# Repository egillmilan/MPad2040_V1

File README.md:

# MPad2040_V1
Numpad based on the RP2040 microcontroller. Uses USB-C and has a macro-row at the top. [Schematic can be found here.](https://github.com/egillmilan/MPad2040_V1/files/11053267/MPad2040_V1.pdf)

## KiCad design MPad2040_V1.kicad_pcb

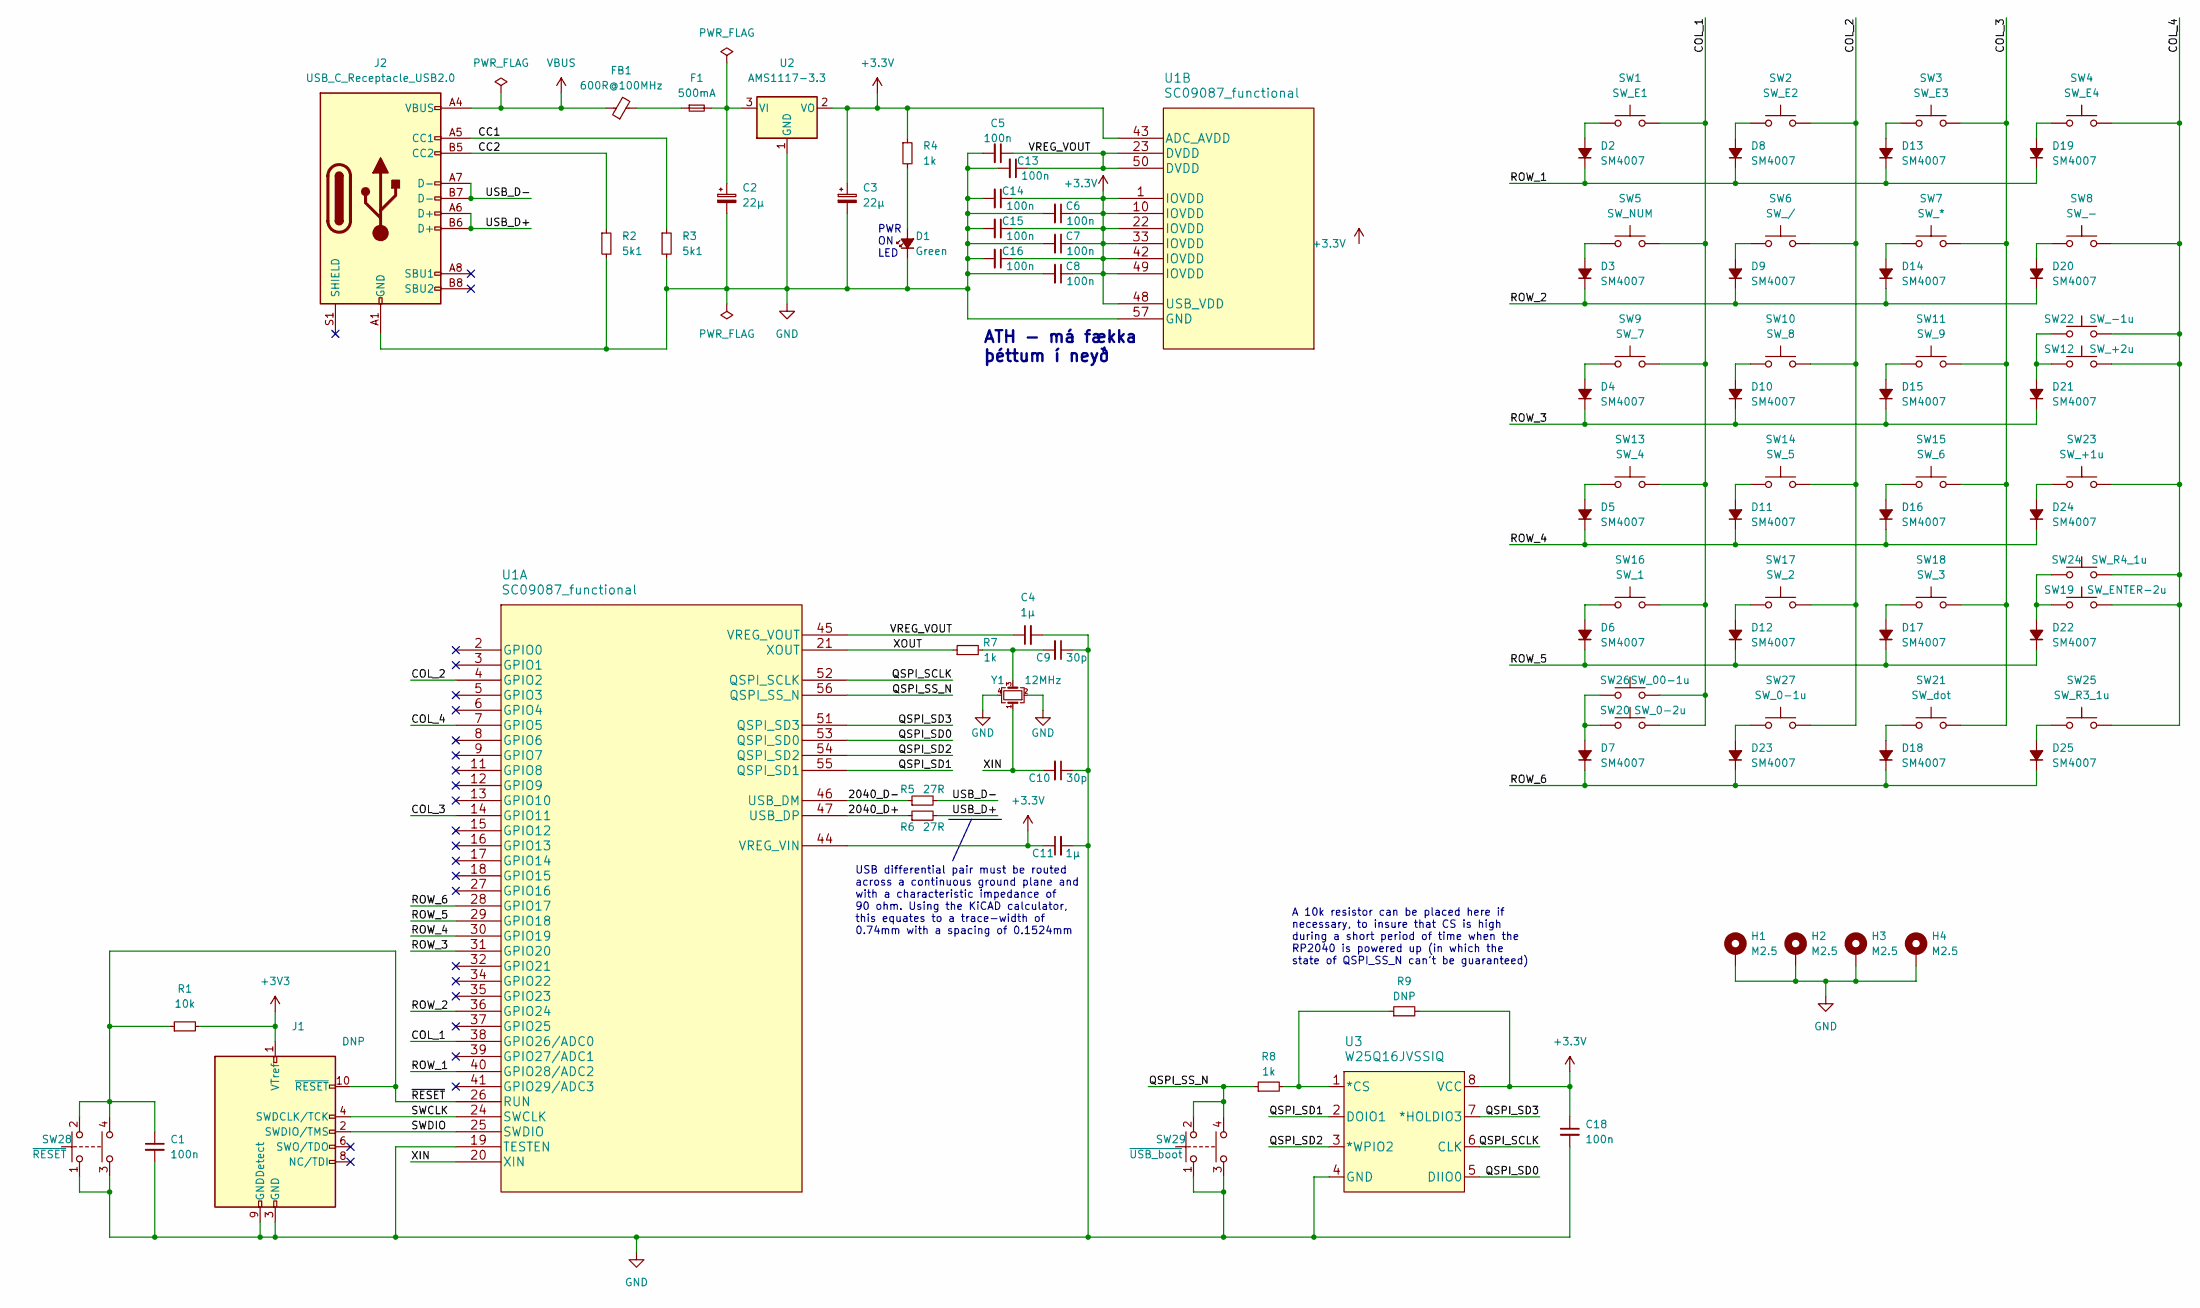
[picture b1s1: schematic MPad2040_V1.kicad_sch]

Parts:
C1, C5, C6, C7, C8, C13, C14, C15, C16, C18: 100n; C_0402_1005Metric
C2, C3: 22µ; CP_EIA-3216-18_Kemet-A
C4, C11: 1µ; C_0402_1005Metric
C9, C10: 30p; C_0402_1005Metric
D1: Green; LED_0603_1608Metric
D2, D3, D4, D5, D6, D7, D8, D9, D10, D11, D12, D13, D14, D15, D16, D17, D18, D19, D20, D21, D22, D23, D24, D25: SM4007; D_SOD-123F
F1: 500mA; Fuse_1206_3216Metric
FB1: 600R@100MHz; L_0603_1608Metric
H1, H2, H3, H4: M2.5; MountingHole_2.7mm_M2.5_Pad_Via
J1: DNP; PinSocket_2x05_P1.27mm_Vertical_SMD
J2: USB_C_Receptacle_USB2.0; USB_C_Receptacle_GCT_USB4085
R1: 10k; R_0603_1608Metric
R2, R3: 5k1; R_0603_1608Metric
R4, R7, R8: 1k; R_0603_1608Metric
R5, R6: 27R; R_0603_1608Metric
R9: DNP; R_0603_1608Metric
SW1: SW_E1; SW_Cherry_MX_1.00u_R1
SW2: SW_E2; SW_Cherry_MX_1.00u_R1
SW3: SW_E3; SW_Cherry_MX_1.00u_R1
SW4: SW_E4; SW_Cherry_MX_1.00u_R1
SW5: SW_NUM; SW_Cherry_MX_1.00u_R1
SW6: SW_/; SW_Cherry_MX_1.00u_R1
SW7: SW_*; SW_Cherry_MX_1.00u_R1
SW8: SW_-; SW_Cherry_MX_1.00u_R1
SW9: SW_7; SW_Cherry_MX_1.00u_R3
SW10: SW_8; SW_Cherry_MX_1.00u_R3
SW11: SW_9; SW_Cherry_MX_1.00u_R3
SW12: SW_+2u; SW_Cherry_MX_2.00u_Vertical_PCB
SW13: SW_4; SW_Cherry_MX_1.00u_R3
SW14: SW_5; SW_Cherry_MX_1.00u_R3
SW15: SW_6; SW_Cherry_MX_1.00u_R3
SW16: SW_1; SW_Cherry_MX_1.00u_R4
SW17: SW_2; SW_Cherry_MX_1.00u_R4
SW18: SW_3; SW_Cherry_MX_1.00u_R4
SW19: SW_ENTER-2u; SW_Cherry_MX_2.00u_Vertical_PCB
SW20: SW_0-2u; SW_Cherry_MX_2.00u_PCB
SW21: SW_dot; SW_Cherry_MX_1.00u_R3
SW22: SW_-1u; SW_Cherry_MX_1.00u_R2
SW23: SW_+1u; SW_Cherry_MX_1.00u_R3
SW24: SW_R4_1u; SW_Cherry_MX_1.00u_R4
SW25: SW_R3_1u; SW_Cherry_MX_1.00u_R3
SW26: SW_00-1u; SW_Cherry_MX_1.00u_R3
SW27: SW_0-1u; SW_Cherry_MX_1.00u_R3
SW28: ~{RESET}; SW_TS-1187A-B-A-B
SW29: ~{USB_boot}; SW_TS-1187A-B-A-B
U1: SC09087_functional; SC09087
U2: AMS1117-3.3; SOT-223-3_TabPin2
U3: W25Q16JVSSIQ
Y1: 12MHz; Crystal_SMD_3225-4Pin_3.2x2.5mm

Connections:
/2040_D+: R6.1, U1.47 (USB_DP)
/2040_D-: R5.1, U1.46 (USB_DM)
/CC1: J2.A5 (CC1), R3.1
/CC2: J2.B5 (CC2), R2.1
/COL_1: SW1.2, SW5.2, SW9.2, SW13.2, SW16.2, SW20.2, SW26.2, U1.38 (GPIO26/ADC0)
/COL_2: SW2.2, SW6.2, SW10.2, SW14.2, SW17.2, SW27.2, U1.4 (GPIO2)
/COL_3: SW3.2, SW7.2, SW11.2, SW15.2, SW18.2, SW21.2, U1.14 (GPIO11)
/COL_4: SW4.2, SW8.2, SW12.2, SW19.2, SW22.2, SW23.2, SW24.2, SW25.2, U1.7 (GPIO5)
/QSPI_SCLK: U1.52 (QSPI_SCLK), U3.6 (CLK)
/QSPI_SD0: U1.53 (QSPI_SD0), U3.5 (DIIO0)
/QSPI_SD1: U1.55 (QSPI_SD1), U3.2 (DOIO1)
/QSPI_SD2: U1.54 (QSPI_SD2), U3.3 (*WPIO2)
/QSPI_SD3: U1.51 (QSPI_SD3), U3.7 (*HOLDIO3)
/QSPI_SS_N: R8.1, SW29.2, SW29.4, U1.56 (QSPI_SS_N)
/ROW_1: D2.1 (K), D8.1 (K), D13.1 (K), D19.1 (K), U1.40 (GPIO28/ADC2)
/ROW_2: D3.1 (K), D9.1 (K), D14.1 (K), D20.1 (K), U1.36 (GPIO24)
/ROW_3: D4.1 (K), D10.1 (K), D15.1 (K), D21.1 (K), U1.31 (GPIO20)
/ROW_4: D5.1 (K), D11.1 (K), D16.1 (K), D24.1 (K), U1.30 (GPIO19)
/ROW_5: D6.1 (K), D12.1 (K), D17.1 (K), D22.1 (K), U1.29 (GPIO18)
/ROW_6: D7.1 (K), D18.1 (K), D23.1 (K), D25.1 (K), U1.28 (GPIO17)
/SWCLK: J1.4 (SWDCLK/TCK), U1.24 (SWCLK)
/SWDIO: J1.2 (SWDIO/TMS), U1.25 (SWDIO)
/USB_D+: J2.A6 (D+), J2.B6 (D+), R6.2
/USB_D-: J2.A7 (D-), J2.B7 (D-), R5.2
/VREG_VOUT: C4.1, C5.1, C13.1, U1.23 (DVDD), U1.45 (VREG_VOUT), U1.50 (DVDD)
/XIN: C10.2, U1.20 (XIN), Y1.1
/XOUT: R7.1, U1.21 (XOUT)
/~RESET: C1.1, J1.10 (~RESET), R1.1, SW28.2, SW28.4, U1.26 (RUN)
GND: C1.2, C2.2, C3.2, C4.2, C5.2, C6.2, C7.2, C8.2, C9.1, C10.1, C11.2, C13.2, C14.2, C15.2, C16.2, C18.2, D1.1 (K), H1.1, H2.1, H3.1, H4.1, J1.3 (GND), J1.5 (GND), J1.9 (GNDDetect), J2.A1 (GND), J2.A12 (GND), J2.B1 (GND), J2.B12 (GND), R2.2, R3.2, SW28.1, SW28.3, SW29.1, SW29.3, U1.19 (TESTEN), U1.57 (GND), U2.1 (GND), U3.4 (GND), Y1.2, Y1.4
unnamed: C2.1, F1.2, U2.3 (VI)
unnamed: C9.2, R7.2, Y1.3
unnamed: D1.2 (A), R4.2
unnamed: D2.2 (A), SW1.1
unnamed: D3.2 (A), SW5.1
unnamed: D4.2 (A), SW9.1
unnamed: D5.2 (A), SW13.1
unnamed: D6.2 (A), SW16.1
unnamed: D7.2 (A), SW20.1, SW26.1
unnamed: D8.2 (A), SW2.1
unnamed: D9.2 (A), SW6.1
unnamed: D10.2 (A), SW10.1
unnamed: D11.2 (A), SW14.1
unnamed: D12.2 (A), SW17.1
unnamed: D13.2 (A), SW3.1
unnamed: D14.2 (A), SW7.1
unnamed: D15.2 (A), SW11.1
unnamed: D16.2 (A), SW15.1
unnamed: D17.2 (A), SW18.1
unnamed: D18.2 (A), SW21.1
unnamed: D19.2 (A), SW4.1
unnamed: D20.2 (A), SW8.1
unnamed: D21.2 (A), SW12.1, SW22.1
unnamed: D22.2 (A), SW19.1, SW24.1
unnamed: D23.2 (A), SW27.1
unnamed: D24.2 (A), SW23.1
unnamed: D25.2 (A), SW25.1
unnamed: F1.1, FB1.2
unnamed: R8.2, R9.1, U3.1 (*CS)
VBUS: FB1.1, J2.A4 (VBUS), J2.A9 (VBUS), J2.B4 (VBUS), J2.B9 (VBUS)

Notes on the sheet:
PWR ON LED
ATH - má fækka þéttum í neyð
A 10k resistor can be placed here if necessary, to insure that CS is high during a short period of time when the RP2040 is powered up (in which the state of QSPI_SS_N can't be guaranteed)
USB differential pair must be routed across a continuous ground plane and with a characteristic impedance of 90 ohm. Using the KiCAD calculator, this equates to a trace-width of 0.74mm with a spacing of 0.1524mm

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
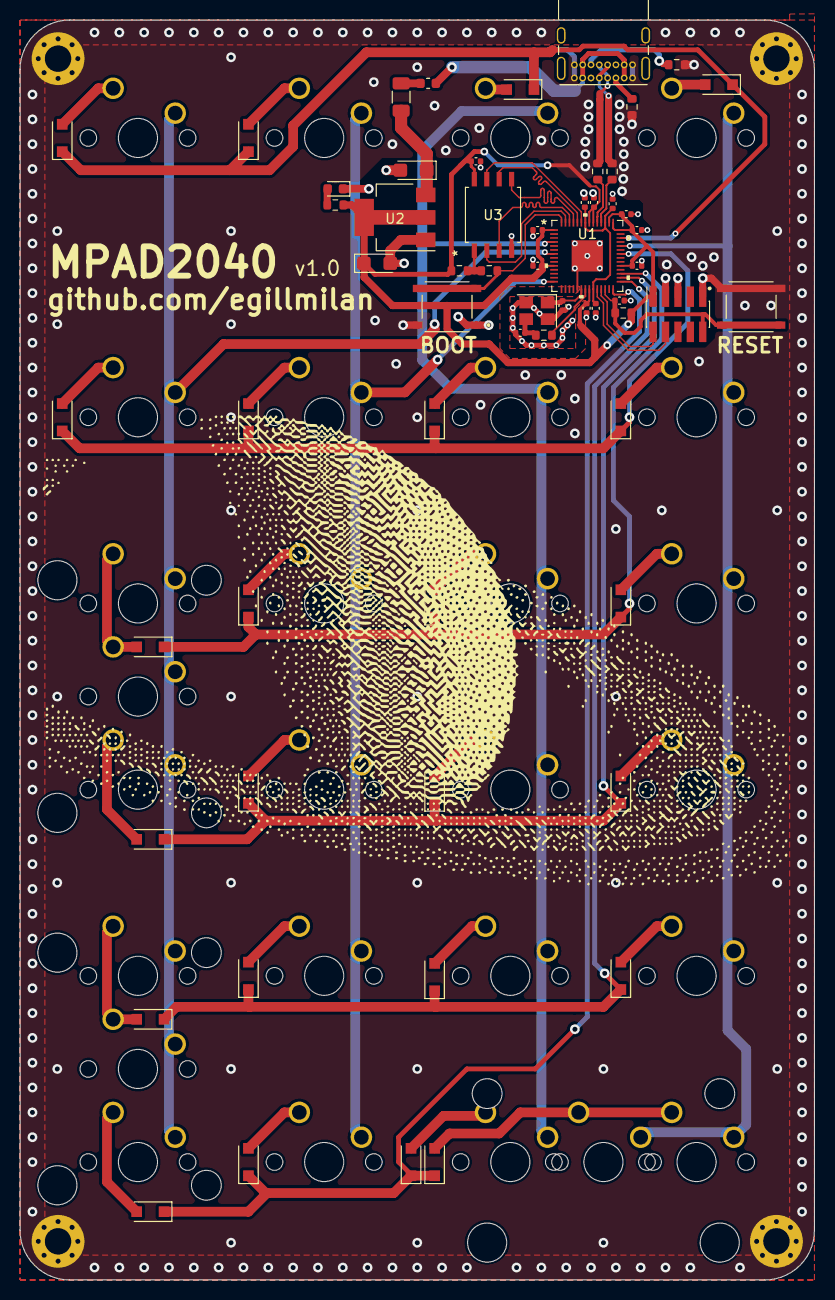
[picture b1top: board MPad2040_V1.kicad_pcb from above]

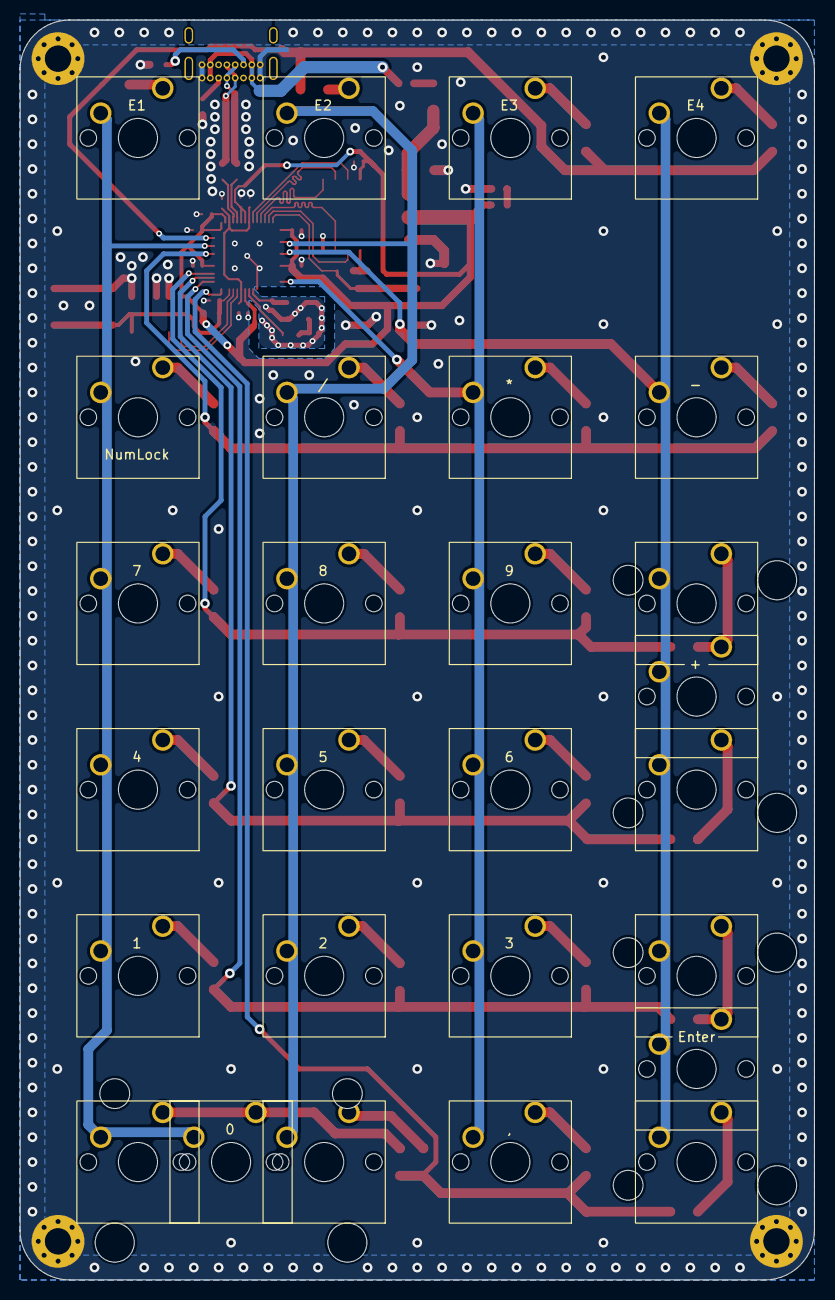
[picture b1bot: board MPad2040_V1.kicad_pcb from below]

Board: 2 copper layers, 81.3 x 128.9 mm, 91 parts (31 on the bottom side), 60 nets.

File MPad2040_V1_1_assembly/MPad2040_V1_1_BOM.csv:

Comment,Designator,Footprint,LCSC Part Number
100nF,"C1, C5, C6, C7, C8, C13, C14, C15, C16, C18",402,C1525
22uF,"C2, C3",CASE-A-3216,C97062
1uF,"C4, C11",402,C52923
30pF,"C9, C10",402,C1570
Green LED,D1,603,C72043
SM4007,"D2, D3, D4, D5, D6, D7, D8, D9, D10, D11, D12, D13, D14, D15, D16, D17, D18, D19, D20, D21, D22, D23, D24, D25",SOD-123FL,C64898
500mA,F1,1206,C206992
220R@100MHz,FB1,603,C80165
USB_C_Receptacle,J2,SMD,C2760486
10k,R1,603,C25804
5k1,"R2, R3",603,C23186
1k,"R4, R7, R8",402,C11702
27R,"R5, R6",402,C226392
TS-1187A-B-A-B,"SW28,SW29",SMD,C318884
RP2040,U1,LQFN-56(7x7),C2040
AMS1117-3.3,U2,SOT-223-3,C6186
W25Q16JVSSIQ,U3,SOIC-8-208mil,C82317
12MHz,Y1,SMD3225-4P,C9002

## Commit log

2023-02-14 Version 1.1 finalized
2023-02-18 Fixes for V1.1
2023-02-24 Font changes on silkscreen
2023-02-27 Added plate
2023-02-27 Ready for production
2023-03-23 update images
2023-08-11 added 3D files
2023-08-11 fixed name
